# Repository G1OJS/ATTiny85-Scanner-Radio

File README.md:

# ATTiny85-Scanner-Radio
Airband Scanner on an ATTiny85 using Si5351 and not much else!

This is a work in progress, but feel free to copy stuff and play with it. The code uses my own minimised Si5351 library which you can find [here](https://github.com/G1OJS/G1OJS_Tiny_Si5351_CLK0). There's also a schematic and a model of the MC1350 that I made from the schematic in the datasheet.

https://github.com/user-attachments/assets/3ad3e072-7772-4eb5-b2a6-2552d3ed8b62

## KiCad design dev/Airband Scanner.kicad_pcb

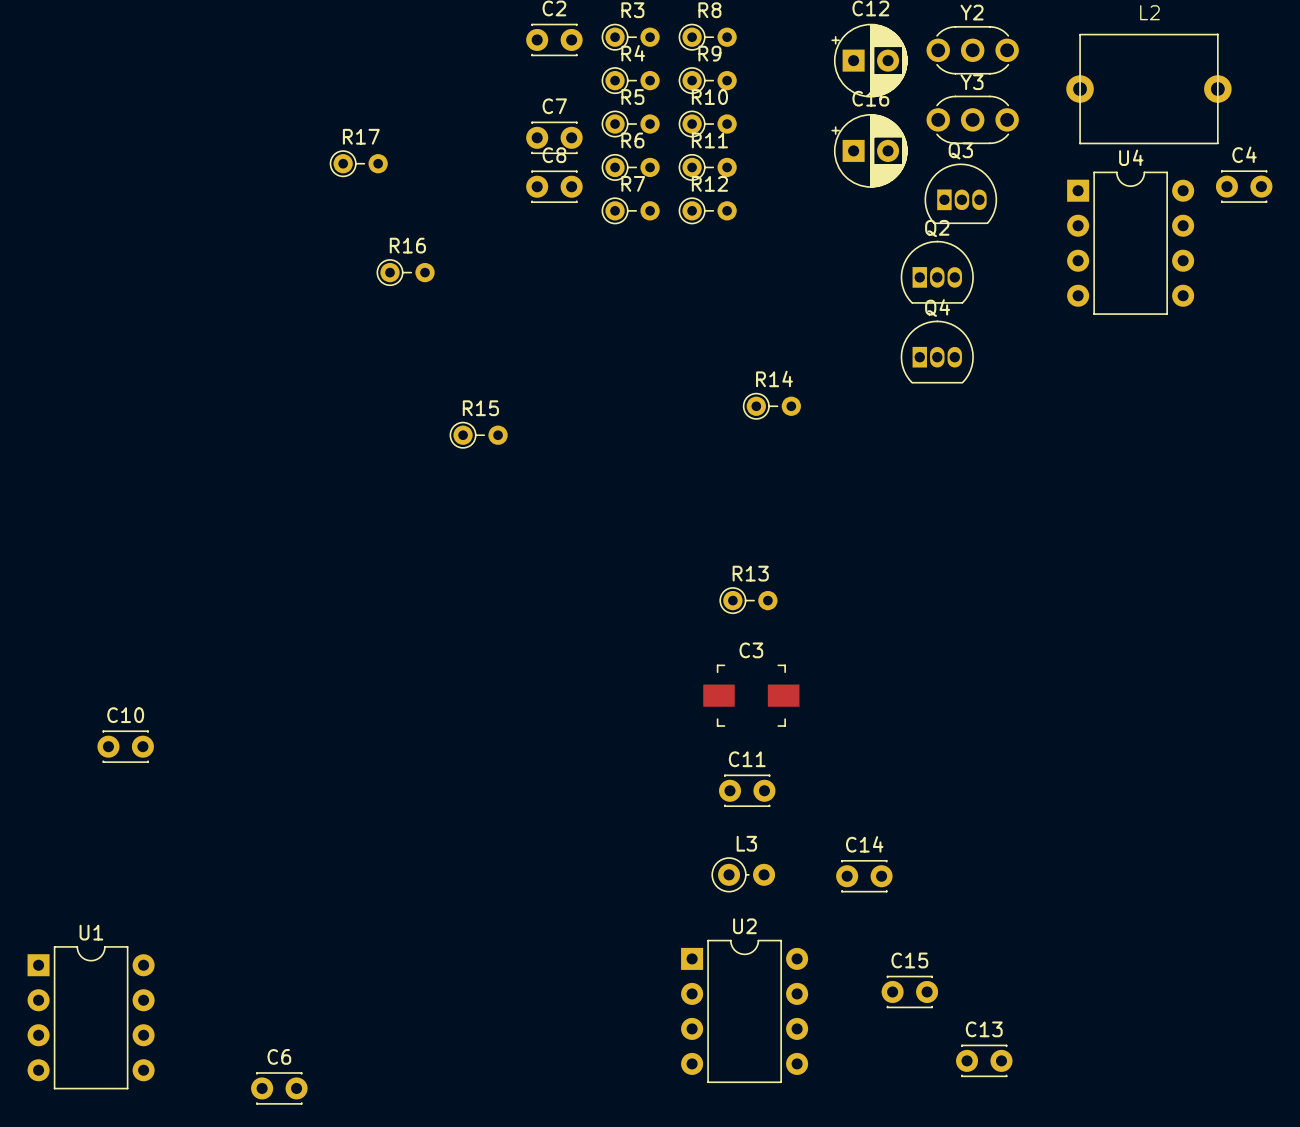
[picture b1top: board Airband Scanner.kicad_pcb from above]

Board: 2 copper layers, 38 parts (0 on the bottom side), 23 nets, no tracks yet.

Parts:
C2: 10nF; C_Disc_D3.0mm_W2.0mm_P2.50mm
C3: 3-18pF; C_Trimmer_Murata_TZB4-A
C4: 3pF; C_Disc_D3.0mm_W2.0mm_P2.50mm
C6, C7: 1n; C_Disc_D3.0mm_W2.0mm_P2.50mm
C8: 47p; C_Disc_D3.0mm_W2.0mm_P2.50mm
C10: 330p; C_Disc_D3.0mm_W2.0mm_P2.50mm
C11: 33pF; C_Disc_D3.0mm_W2.0mm_P2.50mm
C12: 1u; CP_Radial_D5.0mm_P2.50mm
C13, C15: 10n; C_Disc_D3.0mm_W2.0mm_P2.50mm
C14: 150p; C_Disc_D3.0mm_W2.0mm_P2.50mm
C16: 1uF; CP_Radial_D5.0mm_P2.50mm
L2: 4.7uH; Inductor_Axial_L10.0mm_D7.9mm_P10.0mm_Horizontal
L3: 4.7uH; L_Axial_L5.3mm_D2.2mm_P2.54mm_Vertical_Vishay_IM-1
Q2, Q4: 2N3904; TO-92_Inline
Q3: BF256B; TO-92L_Inline
R3: 6k8; R_Axial_DIN0204_L3.6mm_D1.6mm_P2.54mm_Vertical
R4: 2k2; R_Axial_DIN0204_L3.6mm_D1.6mm_P2.54mm_Vertical
R5: 330; R_Axial_DIN0204_L3.6mm_D1.6mm_P2.54mm_Vertical
R6: 150; R_Axial_DIN0204_L3.6mm_D1.6mm_P2.54mm_Vertical
R7: 4k7; R_Axial_DIN0204_L3.6mm_D1.6mm_P2.54mm_Vertical
R8: 100k; R_Axial_DIN0204_L3.6mm_D1.6mm_P2.54mm_Vertical
R9: 1k5; R_Axial_DIN0204_L3.6mm_D1.6mm_P2.54mm_Vertical
R10: 33k; R_Axial_DIN0204_L3.6mm_D1.6mm_P2.54mm_Vertical
R11: 1k; R_Axial_DIN0204_L3.6mm_D1.6mm_P2.54mm_Vertical
R12: 270; R_Axial_DIN0204_L3.6mm_D1.6mm_P2.54mm_Vertical
R13: 470k; R_Axial_DIN0204_L3.6mm_D1.6mm_P2.54mm_Vertical
R14: 10k; R_Axial_DIN0204_L3.6mm_D1.6mm_P2.54mm_Vertical
R15: 560; R_Axial_DIN0204_L3.6mm_D1.6mm_P2.54mm_Vertical
R16: 600; R_Axial_DIN0204_L3.6mm_D1.6mm_P2.54mm_Vertical
R17: 820; R_Axial_DIN0204_L3.6mm_D1.6mm_P2.54mm_Vertical
U1: NE612; DIP-8_W7.62mm
U2: MC1350; DIP-8_W7.62mm
U4: ATtiny85-20P; DIP-8_W7.62mm
Y2, Y3: Resonator; Resonator_Murata_CSTLSxxxX-3Pin_W5.5mm_H3.0mm

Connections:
/Control and DDS/5V: C3.1, C11.1, L3.1, Q3.3 (D), R3.1, R5.1, R13.1, R16.1, U1.8 (Vcc), U2.1 (Out_a), U2.2 (Vcc), U4.8 (VCC)
/Control and DDS/GND: C2.1, C10.2, C12.2, C13.2, C15.2, Q4.1 (E), R4.2, R6.2, R8.2, R10.2, R17.2, U1.3 (GND), U2.7 (GND), U4.4 (GND), Y2.2, Y3.2
/Control and DDS/LO_clean: C4.1, U1.6 (Osc_b)
unnamed: C4.2, L2.1
unnamed: C6.2, R17.1
unnamed: C7.1, R15.1
unnamed: C8.1, R9.1
unnamed: C16.2, R11.1
unnamed: C8.2, Q2.2 (B), R3.2, R4.1
unnamed: Q2.3 (C), R5.2, R12.2
unnamed: C10.1, Q2.1 (E), R6.1
unnamed: C14.2, Q3.1 (G), R8.1
unnamed: C15.1, C16.1, Q3.2 (S), R10.1, R14.2
unnamed: C7.2, Q4.2 (B)
unnamed: Q4.3 (C), R16.2, Y3.1
unnamed: R12.1, Y2.1
unnamed: R15.2, Y2.3
unnamed: C2.2, U1.2 (IN_b)
unnamed: R9.2, U1.4 (OUT_a)
unnamed: C6.1, U2.4 (In_a), Y3.3
unnamed: C13.1, U2.6 (In_b)
unnamed: C3.2, C11.2, C14.1, L3.2, R13.2, U2.8 (Out_b)
unnamed: C12.1, R7.2, U2.5 (V_AGC_in)

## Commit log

2025-06-14 Initial files mainly for backup
    Some files need completing e.g. KiCad schematic.
2025-06-15 Most recent testing version
2025-06-15 Rename Airband Scanner.kicad.png to Schematics/Airband Scanner.kicad.png
2025-06-15 Rename Airband Scanner Control and DDS.kicad.png to Schematics/Airband Scanner Control and DDS.kicad.png
2025-06-15 Rename AirbandScannerAtTiny85.ino to ATTiny85-Sketch/AirbandScannerAtTiny85.ino
2025-06-15 Rename Ceramic_Filter_v1_10704_kHz_600_Ohms.asc to LtSpice/Ceramic_Filter_v1_10704_kHz_600_Ohms.asc
2025-06-15 Rename LtSpice/Ceramic_Filter_v1_10704_kHz_600_Ohms.asc to LtSpice/LT10.7MFP/Ceramic_Filter_v1_10704_kHz_600_Ohms.asc
2025-06-15 Rename MC1350_from_schematic.asc to LtSpice/MC1350/MC1350_from_schematic.asc
2025-07-13 Add local files
